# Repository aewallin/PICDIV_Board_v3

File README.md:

# PICDIV_Board_v3
Programmable 10 MHz to 1PPS frequency divider-board.

The input frequency (sine or square-wave) is first converted to a square-wave and then used as the clock source for a PIC12F675 programmed with the PICDIV firmware (https://github.com/aewallin/PICDIV). Two IDT 5PB1108 buffered outputs are provided. Trimmer-capacitors can be used to accurately tune channel-skew. An LED driven by a timer LTC6993 provides indication of 1PPS signal. A Sync input allows synchronizing the output-1PPS to an input-1PPS, within 100ns (with a 10 MHz clock).

## Firmware

- assembler & build-instructions: https://github.com/aewallin/PICDIV
- original source: http://www.leapsecond.com/pic/picdiv.htm

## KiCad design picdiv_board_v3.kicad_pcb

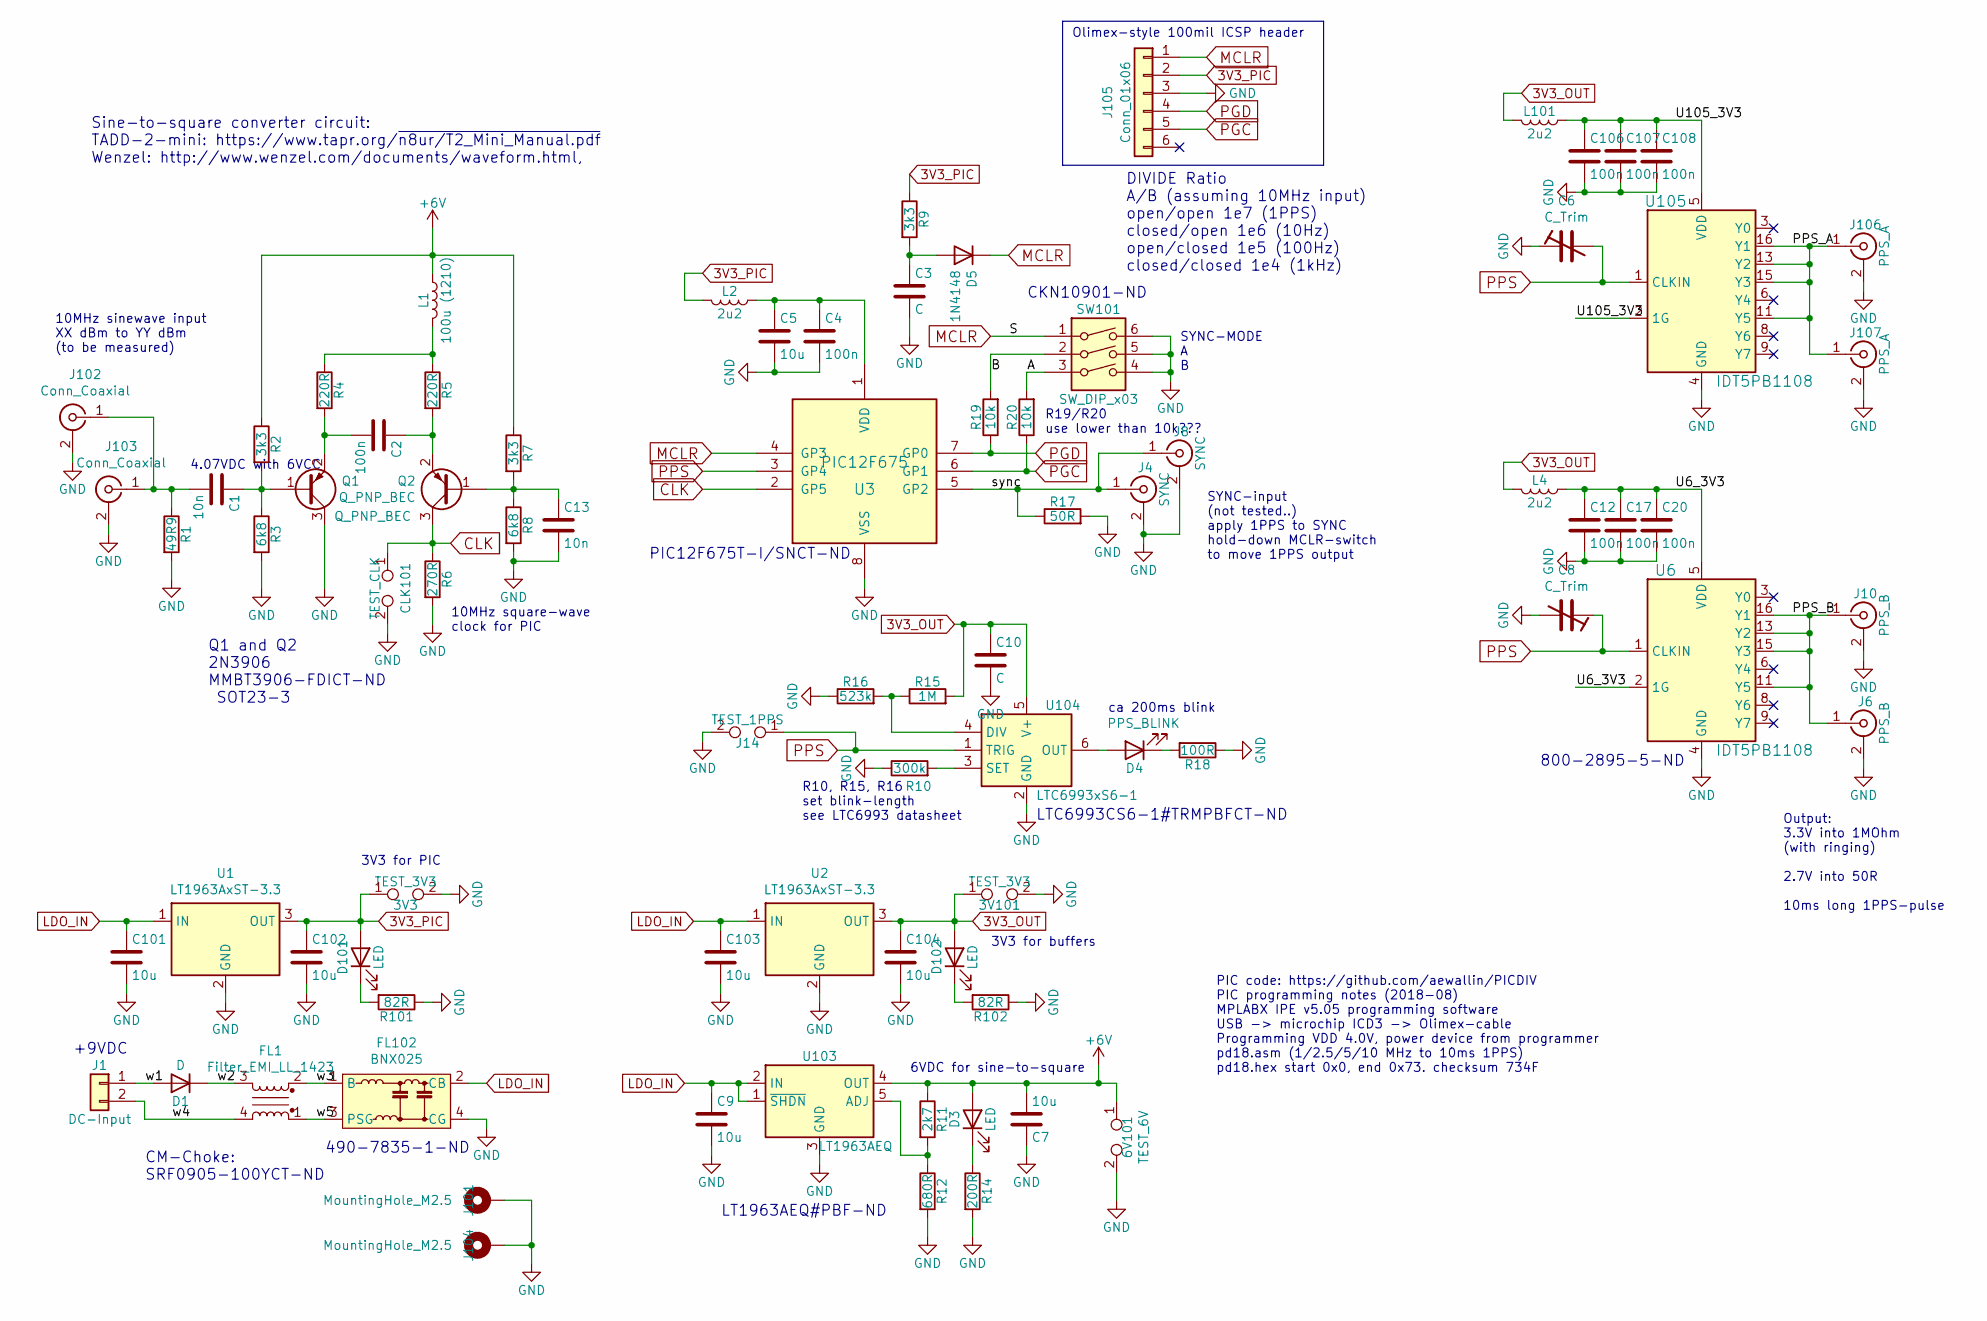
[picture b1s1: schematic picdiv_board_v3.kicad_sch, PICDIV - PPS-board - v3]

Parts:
3V3, 3V101: TEST_3V3; TestPoint_2Pads_Pitch2.54mm_Drill0.8mm
6V101: TEST_6V; TestPoint_2Pads_Pitch2.54mm_Drill0.8mm
C1, C13: 10n; C_0805_2012Metric
C2, C4, C12, C17, C20, C106, C107, C108: 100n; C_0805_2012Metric
C3, C10: C; C_0805_2012Metric
C5, C7, C9, C101, C102, C103, C104: 10u; C_0805_2012Metric
C6, C8: C_Trim; C_Trimmer_Murata_TZB4-A
CLK101: TEST_CLK; TestPoint_2Pads_Pitch2.54mm_Drill0.8mm
D1: D; DIODE_DO-214BA
D3, D101, D102: LED; LED_0805_2012Metric
D4: PPS_BLINK; LED_0805_2012Metric
D5: 1N4148; D_SOD-123
FL1: Filter_EMI_LL_1423; Filter_Bourns_SRF0905_6.0x9.2mm
FL102: BNX025; Filter_Murata_BNX025_ThermalVias
J1: DC-Input; TerminalBlock_bornier-2_P5.08mm
J4: SYNC; SMA_Molex_73251-2200_Horizontal
J6: PPS_B; SMA_Molex_73251-2200_Horizontal
J8: SYNC; BNC_Amphenol_B6252HB-NPP3G-50_Horizontal
J10: PPS_B; BNC_Amphenol_B6252HB-NPP3G-50_Horizontal
J14: TEST_1PPS; TestPoint_2Pads_Pitch2.54mm_Drill0.8mm
J101, J104: MountingHole_M2.5; MountingHole_2.7mm_M2.5_DIN965_Pad
J102: Conn_Coaxial; BNC_Amphenol_B6252HB-NPP3G-50_Horizontal
J103: Conn_Coaxial; SMA_Molex_73251-2200_Horizontal
J105: Conn_01x06; PinHeader_1x06_P2.54mm_Vertical
J106: PPS_A; BNC_Amphenol_B6252HB-NPP3G-50_Horizontal
J107: PPS_A; SMA_Molex_73251-2200_Horizontal
L1: 100u (1210); L_1210_3225Metric
L2, L4, L101: 2u2; L_0805_2012Metric
Q1, Q2: Q_PNP_BEC; SOT-23
R1: 49R9; R_0805_2012Metric
R2, R7, R9: 3k3; R_0805_2012Metric
R3, R8: 6k8; R_0805_2012Metric
R4, R5: 220R; R_0805_2012Metric
R6: 270R; R_0805_2012Metric
R10: 300k; R_0805_2012Metric
R11: 2k7; R_0805_2012Metric
R12: 680R; R_0805_2012Metric
R14: 200R; R_0805_2012Metric
R15: 1M; R_0805_2012Metric
R16: 523k; R_0805_2012Metric
R17: 50R; R_0805_2012Metric
R18: 100R; R_0805_2012Metric
R19, R20: 10k; R_0805_2012Metric
R101, R102: 82R; R_0805_2012Metric
SW101: SW_DIP_x03; SW_DIP_SPSTx03_Slide_6.7x9.18mm_W8.61mm_P2.54mm_LowProfile
U1, U2: LT1963AxST-3.3; SOT-223-3_TabPin2
U3: PIC12F675; SOIC-8_3.9x4.9mm_P1.27mm
U6, U105: IDT5PB1108; TSSOP-16_4.4x5mm_P0.65mm
U103: LT1963AEQ; TO-263-5_TabPin3
U104: LTC6993xS6-1; TSOT-23-6

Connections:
3V3_OUT: 3V101.1, C10.1, C104.1, D102.2 (A), L4.2, L101.2, R15.2, U2.3 (OUT), U104.5 (V+)
3V3_PIC: 3V3.1, C102.1, D101.2 (A), J105.2, L2.2, R9.1, U1.3 (OUT)
+6V: 6V101.1, C7.2, D3.2 (A), L1.1, R2.1, R7.1, R11.1, U103.4 (OUT)
/A: R20.2, SW101.3
/B: R19.2, SW101.2
/PPS_A: J106.1 (In), J107.1 (In), U105.11 (Y5), U105.13 (Y2), U105.15 (Y3), U105.16 (Y1)
/PPS_B: J6.1 (In), J10.1 (In), U6.11 (Y5), U6.13 (Y2), U6.15 (Y3), U6.16 (Y1)
/U6_3V3: C12.1, C17.1, C20.1, L4.1, U6.2 (1G), U6.5 (VDD), U6.10 (VDD), U6.14 (VDD)
/U105_3V3: C106.1, C107.1, C108.1, L101.1, U105.2 (1G), U105.5 (VDD), U105.10 (VDD), U105.14 (VDD)
/sync: J4.1 (In), J8.1 (In), R17.1, U3.5 (GP2)
/w1: D1.2 (A), J1.1
/w2: D1.1 (K), FL1.3
/w3: FL1.2, FL102.1 (B)
/w4: FL1.4, J1.2
/w5: FL1.1, FL102.3 (PSG)
CLK: CLK101.1, Q2.3 (C), R6.1, U3.2 (GP5)
GND: 3V3.2, 3V101.2, 6V101.2, C3.2, C4.2, C5.2, C6.1, C7.1, C8.2, C9.2, C10.2, C12.2, C13.2, C17.2, C20.2, C101.2, C102.2, C103.2, C104.2, C106.2, C107.2, C108.2, CLK101.2, FL102.4 (CG), J4.2 (Ext), J6.2 (Ext), J8.2 (Ext), J10.2 (Ext), J14.2, J101.1, J102.2 (Ext), J103.2 (Ext), J104.1, J105.3, J106.2 (Ext), J107.2 (Ext), Q1.3 (C), R1.2, R3.2, R6.2, R8.2, R10.1, R12.2, R14.2, R16.1, R17.2, R18.1, R101.1, R102.1, SW101.4, SW101.5, SW101.6, U1.2 (GND), U2.2 (GND), U3.8 (VSS), U6.4 (GND), U6.7 (GND), U6.12 (GND), U103.3 (GND), U104.2 (GND), U105.4 (GND), U105.7 (GND), U105.12 (GND)
LDO_IN: C9.1, C101.1, C103.1, FL102.2 (CB), U1.1 (IN), U2.1 (IN), U103.1 (~SHDN), U103.2 (IN)
MCLR: D5.1 (K), J105.1, SW101.1, U3.4 (GP3)
unnamed: C1.1, Q1.1 (B), R2.2, R3.1
unnamed: C1.2, J102.1 (In), J103.1 (In), R1.1
unnamed: C2.1, Q2.2 (E), R5.2
unnamed: C2.2, Q1.2 (E), R4.2
unnamed: C3.1, D5.2 (A), R9.2
unnamed: C4.1, C5.1, L2.1, U3.1 (VDD)
unnamed: C13.1, Q2.1 (B), R7.2, R8.1
unnamed: D3.1 (K), R14.1
unnamed: D4.1 (K), R18.2
unnamed: D4.2 (A), U104.6 (OUT)
unnamed: D101.1 (K), R101.2
unnamed: D102.1 (K), R102.2
unnamed: L1.2, R4.1, R5.1
unnamed: R10.2, U104.3 (SET)
unnamed: R11.2, R12.1, U103.5 (ADJ)
unnamed: R15.1, R16.2, U104.4 (DIV)
PGC: J105.5, R20.1, U3.6 (GP1)
PGD: J105.4, R19.1, U3.7 (GP0)
PPS: C6.2, C8.1, J14.1, U3.3 (GP4), U6.1 (CLKIN), U104.1 (TRIG), U105.1 (CLKIN)

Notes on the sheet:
LT1963AEQ#PBF-ND
PIC code: https://github.com/aewallin/PICDIV PIC programming notes (2018-08) MPLABX IPE v5.05 programming software USB -> microchip ICD3 -> Olimex-cable Programming VDD 4.0V, power device from programmer pd18.asm (1/2.5/5/10 MHz to 10ms 1PPS) pd18.hex start 0x0, end 0x73. checksum 734F
+9VDC
10MHz square-wave clock for PIC
DIVIDE Ratio A/B (assuming 10MHz input) open/open 1e7 (1PPS) closed/open 1e6 (10Hz) open/closed 1e5 (100Hz) closed/closed 1e4 (1kHz)
Output: 3.3V into 1MOhm (with ringing) 2.7V into 50R 10ms long 1PPS-pulse
ca 200ms blink
SYNC-MODE A B
R10, R15, R16 set blink-length see LTC6993 datasheet
LTC6993CS6-1#TRMPBFCT-ND
CKN10901-ND
3V3 for buffers
Sine-to-square converter circuit: TADD-2-mini: https://www.tapr.org/~{n8ur/T2_Mini_Manual.pdf} Wenzel: http://www.wenzel.com/documents/waveform.html,
CM-Choke: SRF0905-100YCT-ND
490-7835-1-ND
Olimex-style 100mil ICSP header
R19/R20 use lower than 10k???
Q1 and Q2 2N3906 MMBT3906-FDICT-ND SOT23-3
800-2895-5-ND
6VDC for sine-to-square
3V3 for PIC
10MHz sinewave input XX dBm to YY dBm (to be measured)
PIC12F675T-I/SNCT-ND
SYNC-input (not tested..) apply 1PPS to SYNC hold-down MCLR-switch to move 1PPS output
4.07VDC with 6VCC

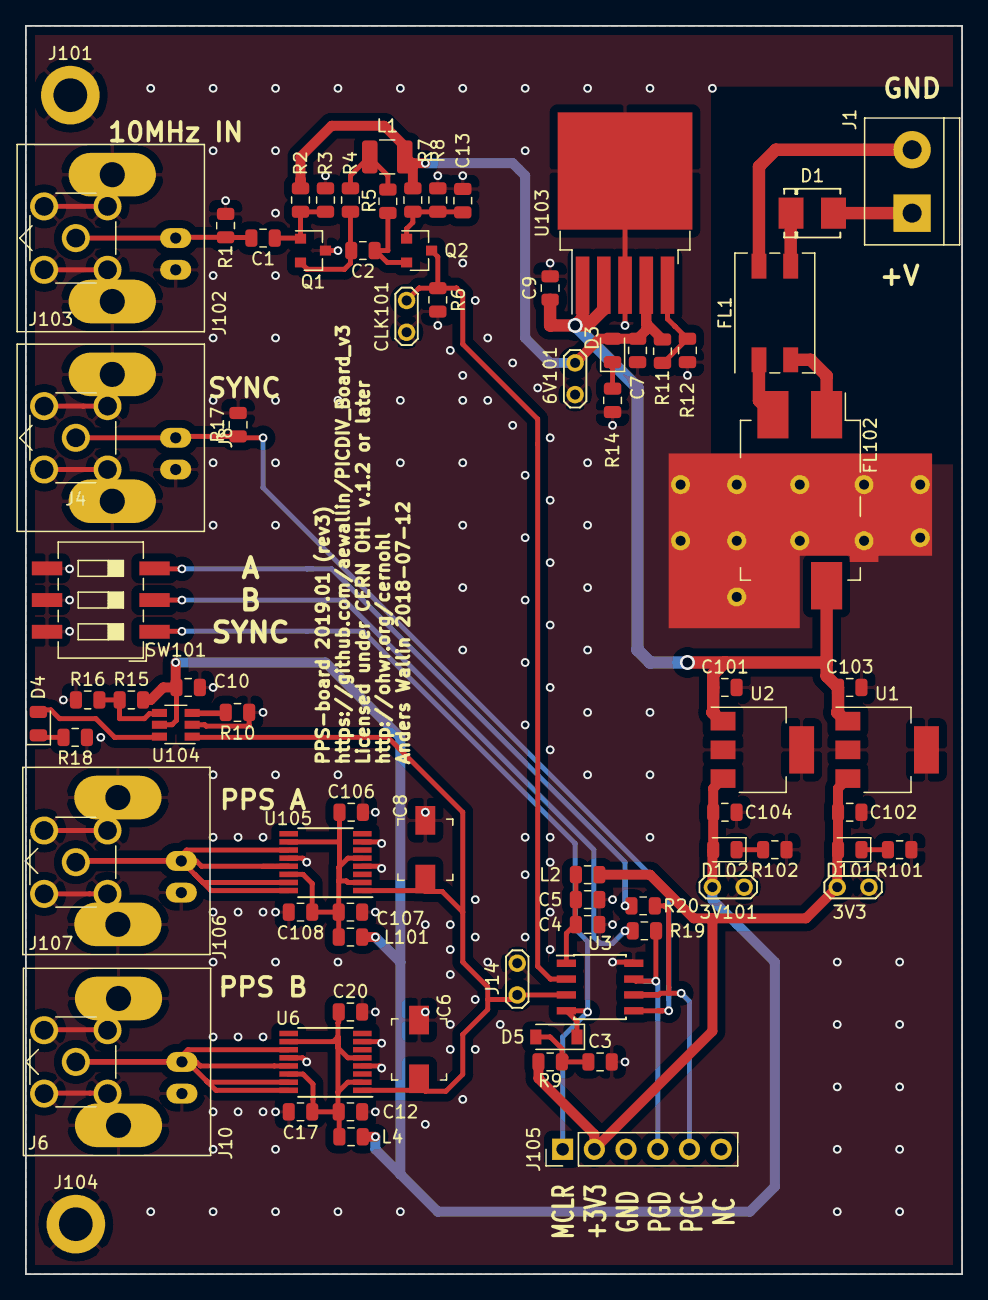
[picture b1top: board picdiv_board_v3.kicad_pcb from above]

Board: 2 copper layers, 75.0 x 100.0 mm, 81 parts (0 on the bottom side), 38 nets.

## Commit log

2019-01-19 links
2019-01-19 initial commit of old files - draft and broken!
2019-01-19 initial layout, symbols to kicad5
2019-01-22 pcb passes DRC
2019-03-16 add descriptions of DC
2019-03-16 add URL to silk
2019-03-16 add 3D view screenshot of PCB
2019-03-16 link image
2019-03-16 gnd-vias, silk, move PPSB connectors.
2021-01-23 minor updates
2021-09-23 fix missing symbols (kicad lib)
2022-12-09 kicad6 version
2022-12-09 remove old kicad5 version
2023-02-14 kicad7

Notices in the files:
picdiv_board_v3.kicad_pcb:
Licensed under CERN OHL v.1.2 or later
